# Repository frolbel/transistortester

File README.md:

# TransistorTester with AVR microcontroller

This repository is based on the software repository of the TransistorTester of Markus F. and Karl-Heinz Kubbeler.

The current revision of the authors you can see on the following: [https://www.mikrocontroller.net/svnbrowser/transistortester/](https://www.mikrocontroller.net/svnbrowser/transistortester/?sortby=author)

Initially, this repository is **GitHub** clone of **SVN** repo svn://mikrocontroller.net/transistortester/

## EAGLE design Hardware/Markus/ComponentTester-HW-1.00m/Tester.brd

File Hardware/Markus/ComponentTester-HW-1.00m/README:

------------------------------------------------------------------------------

                  ReadMe for the Component Tester Hardware

         (c) 2013 by Markus Reschke (madires@theca-tabellaria.de)

------------------------------------------------------------------------------

Last edit:  2013-03-22

* About

The Component Tester is based on the project of Markus Frejek [1&2] and the
successor of Karl-Heinz Kübbeler [3&4].

* Safety Advice

The Component Tester is no DMM! It's a simple tester for components capable
of measuring several things. The probes aren't protected in any way and
won't survive higher voltages than 5V. Don't use the tester for live circuits!
Just use it for unsoldered electronic components! If you test a capacitor make
sure it's discharged before connecting the probes. This isn't just the Safety
Sally, your life may be at risk if you connect the probes to a live circuit
or a power supply (or even mains). 

* What's different?

Karl-Heinz has done a realy great documentation of the tester. I recommend
to read it. Therefore I'll tell you just about the differences to the
official release.

* What's in the box?

Following files are in the archive:
- this README
- schematics in PDF format
- schematics and PCB layout for Eagle 6.4.0
- pictures of my Component Tester

* Circuit

The circuit was extended with a current limiting PWM driver for the LED
backlight of the LCD module. The PWM circuit is based on an idea of
Eberhard Haug [5]. You'll find the details of the current sensing resistor
for the current limiter in the schematics. Calculate the proper resistor
values for the LCD module you're using.

The tester has two power supply inputs, one for battery operation (9V) and
another for an external power supply. The LCD backlight is powered by the
latter input only. The supply voltage shouldn't exceed 12VDC because the
low drop voltage regulator supports 13.2V at maximum (add 0.7V for the
reverse protection diode).

* Layout

The layout is optimized for a benchtop-type box and home lab PCB production
without through-hole plating. I recommend to use precision sockets for both
ICs. They allow to solder the pins at the top layer without much trouble.
You might need to grind the top layer pads for the crystal to prevent any
short circuit of the leads via the metal case. Also the drill diameter of
the pads for the ISP pinheader connector could require some rework.

* References

[1] AVR-Transistortester, Markus Frejek,
    Embedded Projects Journal, 2011-11

[2] http://www.mikrocontroller.net/topic/131804
    thread of Markus Frejek, Forum, 2009

[3] http://www.mikrocontroller.net/articles/AVR-Transistortester
    Online documentation of the Transistortester, Online Article, 2009-2011

[4] http://www.mikrocontroller.net/articles/AVR_Transistortester
    Short description of the TransistorTester, Karl-Heinz Kübbeler,
    Online Article, 2012

[5] http://www.led-treiber.de/html/leds_grundlagen.html#PWM-Dimmer
    Description of a LM339 based PWM circuit, Eberhard Haug.

------------------------------------ EOF -------------------------------------

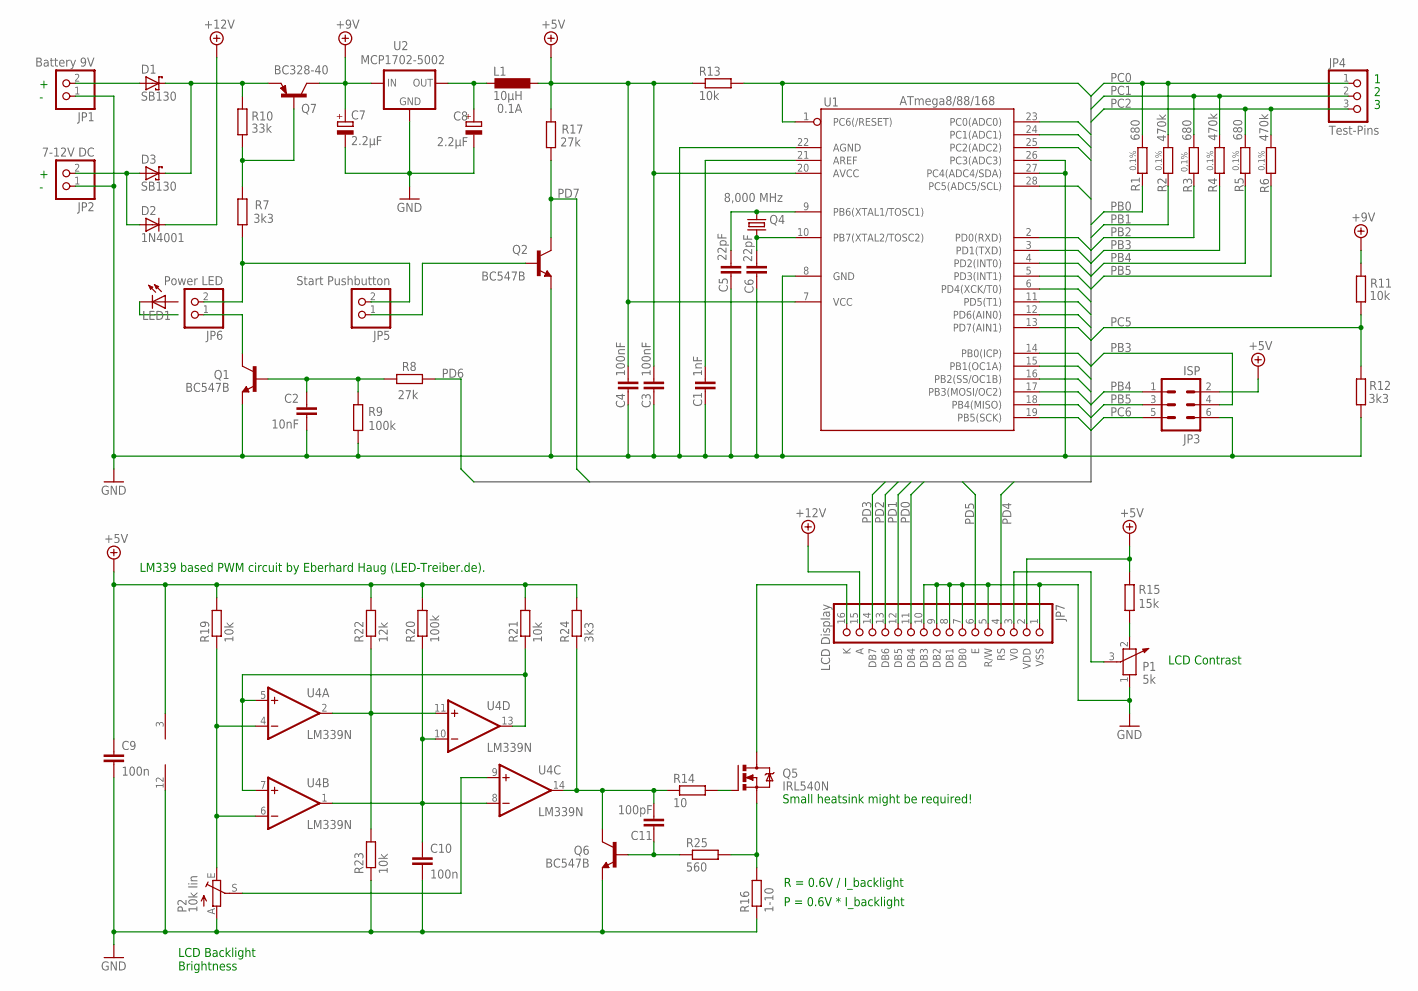
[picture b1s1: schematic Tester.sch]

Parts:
C1: 1nF; C2.5-2
C2: 10nF; C2.5-3
C3, C4: 100nF; C5B3
C5, C6: 22pF; C2.5-3
C7, C8: 2.2µF; E5-5
C9, C10: 100n; C050-024X044
C11: 100pF; C2.5-2
D1, D3: SB130; DIODE-3-5A-V
D2: 1N4001; DIODE-3-5A-V
JP1: Battery 9V; PINHD-1X02
JP2: 7-12V DC; PINHD-1X02
JP3: ISP; ML6
JP4: Test-Pins; PINHD-1X03
JP5: Start Pushbutton; PINHD-1X02
JP6: Power LED; PINHD-1X02
JP7: LCD Display; PINHD-1X16
L1: 10µH; 0204/7
P1: 5k; PT-10
P2: 10k lin; LI10
Q1, Q2, Q6: BC547B; TO92
Q4: 8,000 MHz; HC49/S
Q5: IRL540N; TO220BV
Q7: BC328-40; TO92-EBC
R1, R5: 680; 0207/10; TOLERANCE 0.1%
R2, R4, R6: 470k; 0207/10; TOLERANCE 0.1%
R3: 680; 0207/10; TOLERANCE 0,1%
R7: 3k3; 0207/10
R8, R17: 27k; 0207/2V
R9: 100k; 0207/2V
R10: 33k; 0207/2V
R11, R19, R21: 10k; 0207/2V
R12: 3k3; 0207/2V
R13: 10k; 0207/10
R14: 10; 0207/2V
R15: 15k; 0207/10
R16: 1-10; 0207/10
R20: 100k; 0207/5V
R22: 12k; 0207/5V
R23: 10k; 0207/5V
R24: 3k3; 0207/5V
R25: 560; 0207/5V
U1: ATmega8/88/168; DIL28-3
U2: MCP1702-5002; TO92-LOWDROP
U4: LM339N; DIL14

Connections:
+5V: C3.2, C4.1, C9.1, JP3.2, JP7.2 (VDD), L1.1, R13.1, R15.1, R17.2, R19.2, R20.2, R21.2, R22.2, R24.2, U1.7 (VCC), U1.20 (AVCC), U4.3 (V+)
+9V: C7.+, Q7.C, R11.1, U2.IN
+12V: D2.C, JP7.15 (A)
BL_K: JP7.16 (K), Q5.D
GND: C1.1, C2.2, C3.1, C4.2, C5.1, C6.1, C7.-, C8.-, C9.2, C10.2, JP1.1, JP2.1, JP3.6, JP7.1 (VSS), JP7.5 (R/W), JP7.7 (DB0), JP7.8 (DB1), JP7.9 (DB2), JP7.10 (DB3), P1.1, P2.A, Q1.1 (E), Q2.1 (E), Q6.1 (E), R9.1, R12.1, R16.1, R23.1, U1.8 (GND), U1.22 (AGND), U1.26 (PC3(ADC3)), U1.27 (PC4(ADC4/SDA)), U2.GND, U4.12 (GND)
unnamed: P1.2, R15.2
unnamed: JP7.3 (V0), P1.3
unnamed: Q5.S, R16.2, R25.2
unnamed: R22.1, R23.2, U4.2 (OUT), U4.11 (+IN)
unnamed: D1.C, D3.C, Q7.E, R10.1
unnamed: C10.1, R20.1, U4.1 (OUT), U4.8 (-IN), U4.10 (-IN)
unnamed: R21.1, U4.5 (+IN), U4.7 (+IN), U4.13 (OUT)
unnamed: JP6.1, Q1.3 (C)
unnamed: D1.A, JP1.2
unnamed: C1.2, U1.21 (AREF)
unnamed: C5.2, Q4.2, U1.9 (PB6(XTAL1/TOSC1))
unnamed: C6.2, Q4.1, U1.10 (PB7(XTAL2/TOSC2))
unnamed: JP5.1, Q2.2 (B)
unnamed: P2.E, R19.1, U4.4 (-IN), U4.6 (-IN)
unnamed: P2.S, U4.9 (+IN)
unnamed: C11.2, Q6.3 (C), R14.1, R24.1, U4.14 (OUT)
unnamed: Q5.G, R14.2
unnamed: C11.1, Q6.2 (B), R25.1
unnamed: C8.+, L1.2, U2.OUT
unnamed: JP5.2, JP6.2, R7.1
unnamed: D2.A, D3.A, JP2.2
unnamed: Q7.B, R7.2, R10.2
unnamed: C2.1, Q1.2 (B), R8.2, R9.2
PB0: R1.1, U1.14 (PB0(ICP))
PB1: R2.1, U1.15 (PB1(OC1A))
PB2: R3.1, U1.16 (PB2(SS/OC1B))
PB3: JP3.4, R4.1, U1.17 (PB3(MOSI/OC2))
PB4: JP3.1, R5.1, U1.18 (PB4(MISO))
PB5: JP3.3, R6.1, U1.19 (PB5(SCK))
PC0: JP4.1, R1.2, R2.2, U1.23 (PC0(ADC0))
PC1: JP4.2, R3.2, R4.2, U1.24 (PC1(ADC1))
PC2: JP4.3, R5.2, R6.2, U1.25 (PC2(ADC2))
PC5: R11.2, R12.2, U1.28 (PC5(ADC5/SCL))
PC6: JP3.5, R13.2, U1.1 (PC6(/RESET))
PD0: JP7.11 (DB4), U1.2 (PD0(RXD))
PD1: JP7.12 (DB5), U1.3 (PD1(TXD))
PD2: JP7.13 (DB6), U1.4 (PD2(INT0))
PD3: JP7.14 (DB7), U1.5 (PD3(INT1))
PD4: JP7.4 (RS), U1.6 (PD4(XCK/T0))
PD5: JP7.6 (E), U1.11 (PD5(T1))
PD6: R8.1, U1.12 (PD6(AIN0))
PD7: Q2.3 (C), R17.1, U1.13 (PD7(AIN1))

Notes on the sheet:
R = 0.6V / I_backlight
P = 0.6V * I_backlight
LCD Contrast
LCD Backlight Brightness
Small heatsink might be required!
LM339 based PWM circuit by Eberhard Haug (LED-Treiber.de).

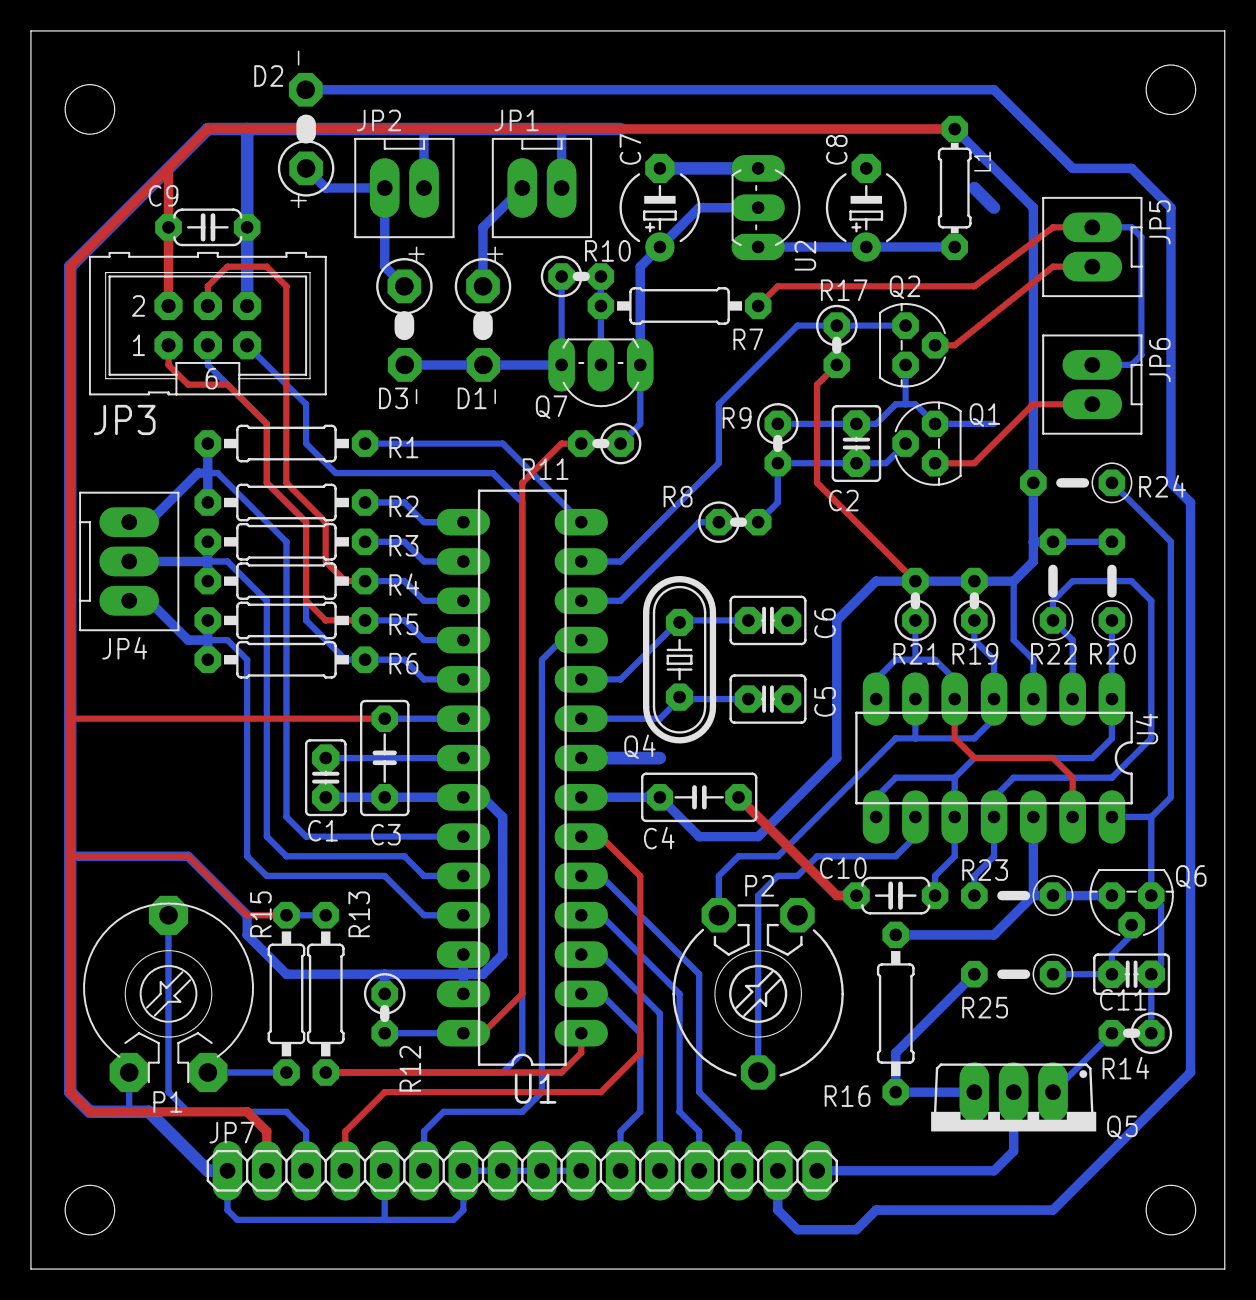
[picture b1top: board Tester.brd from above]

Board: 2 copper layers, 77.1 x 80.0 mm, 57 parts (0 on the bottom side), 47 nets.

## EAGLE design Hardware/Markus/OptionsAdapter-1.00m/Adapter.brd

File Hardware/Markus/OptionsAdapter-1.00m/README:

------------------------------------------------------------------------------

              ReadMe for the Component Tester's Options Adapter

         (c) 2014 by Markus Reschke (madires@theca-tabellaria.de)

------------------------------------------------------------------------------

Last edit:  2014-08-11

* About

The Component Tester is based on the project of Markus Frejek [1&2] and the
successor project of Karl-Heinz Kübbeler [3&4]. The Options Adapter provides
a simple way to extend the basic tester with a rotary encoder for the user
interface and an input stage for the frequency counter function. Both
options are based on the circuits of Karl-Heinz Kübbeler.

* Safety Advice

The Options Adapter doesn't provide any input protection for the frequency
counter besides the AC coupling cap. Don't connect any signal sources with
voltages higher than 5V!

* What's in the box?

Following files are in the archive:
- this README
- schematics in PDF format
- schematics and PCB layout for Eagle 6.5.0 or later
- pictures of my Component Tester with the Options Adapter

* Layout

The layout is optimized for a benchtop-type box and home lab PCB production.
It allows you to mount the adapter perpendicular on the LCD module or in
piggy-back style. You just need to change the pinheaders accordingly.

* References

[1] AVR-Transistortester, Markus Frejek,
    Embedded Projects Journal, 2011-11

[2] http://www.mikrocontroller.net/topic/131804
    thread of Markus Frejek, Forum, 2009

[3] http://www.mikrocontroller.net/articles/AVR-Transistortester
    Online documentation of the Transistortester, Online Article, 2009-2011

[4] http://www.mikrocontroller.net/articles/AVR_Transistortester
    Short description of the TransistorTester, Karl-Heinz Kübbeler,
    Online Article, 2012

------------------------------------ EOF -------------------------------------

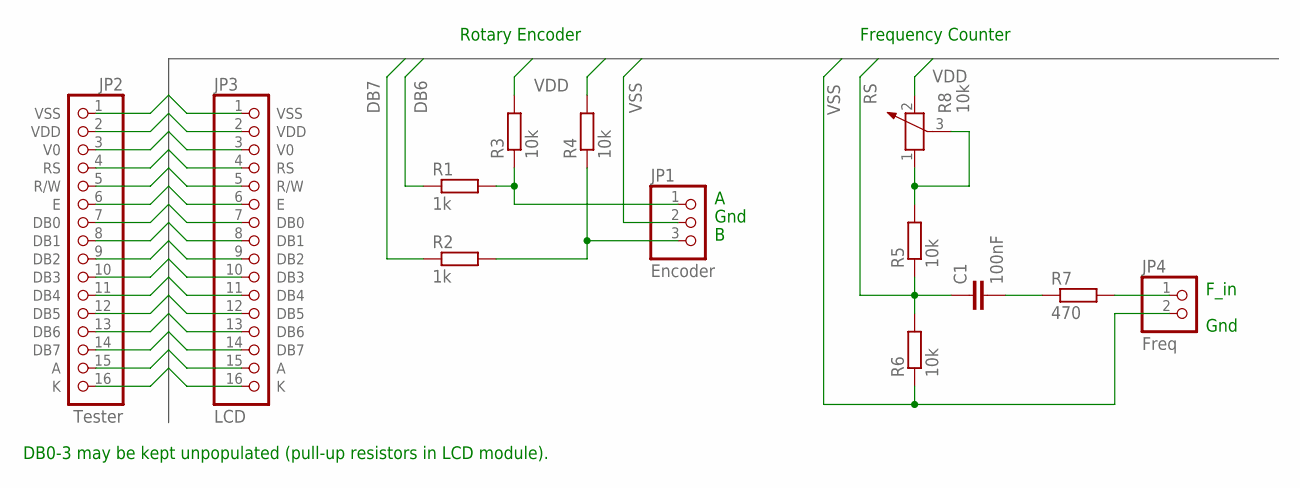
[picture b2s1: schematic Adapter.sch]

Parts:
C1: 100nF; C050-025X075
JP1: Encoder; PINHD-1X03
JP2: Tester; PINHD-1X16
JP3: LCD; PINHD-1X16
JP4: Freq; PINHD-1X02
R1, R2: 1k; 0207/10
R3, R4, R5, R6: 10k; 0207/5V
R7: 470; 0207/5V
R8: 10k; PT-10

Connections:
A: JP2.15 (A), JP3.15 (A)
DB0: JP2.7 (DB0), JP3.7 (DB0)
DB1: JP2.8 (DB1), JP3.8 (DB1)
DB2: JP2.9 (DB2), JP3.9 (DB2)
DB3: JP2.10 (DB3), JP3.10 (DB3)
DB4: JP2.11 (DB4), JP3.11 (DB4)
DB5: JP2.12 (DB5), JP3.12 (DB5)
DB6: JP2.13 (DB6), JP3.13 (DB6), R1.1
DB7: JP2.14 (DB7), JP3.14 (DB7), R2.1
E: JP2.6 (E), JP3.6 (E)
ENC_A: JP1.1, R1.2, R3.1
ENC_B: JP1.3, R2.2, R4.1
K: JP2.16 (K), JP3.16 (K)
unnamed: JP4.1, R7.2
unnamed: R5.2, R8.1, R8.3
unnamed: C1.2, R7.1
RS: C1.1, JP2.4 (RS), JP3.4 (RS), R5.1, R6.2
RW: JP2.5 (R/W), JP3.5 (R/W)
V0: JP2.3 (V0), JP3.3 (V0)
VDD: JP2.2 (VDD), JP3.2 (VDD), R3.2, R4.2, R8.2
VSS: JP1.2, JP2.1 (VSS), JP3.1 (VSS), JP4.2, R6.1

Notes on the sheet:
Gnd
Rotary Encoder
Frequency Counter
F_in
DB0-3 may be kept unpopulated (pull-up resistors in LCD module).

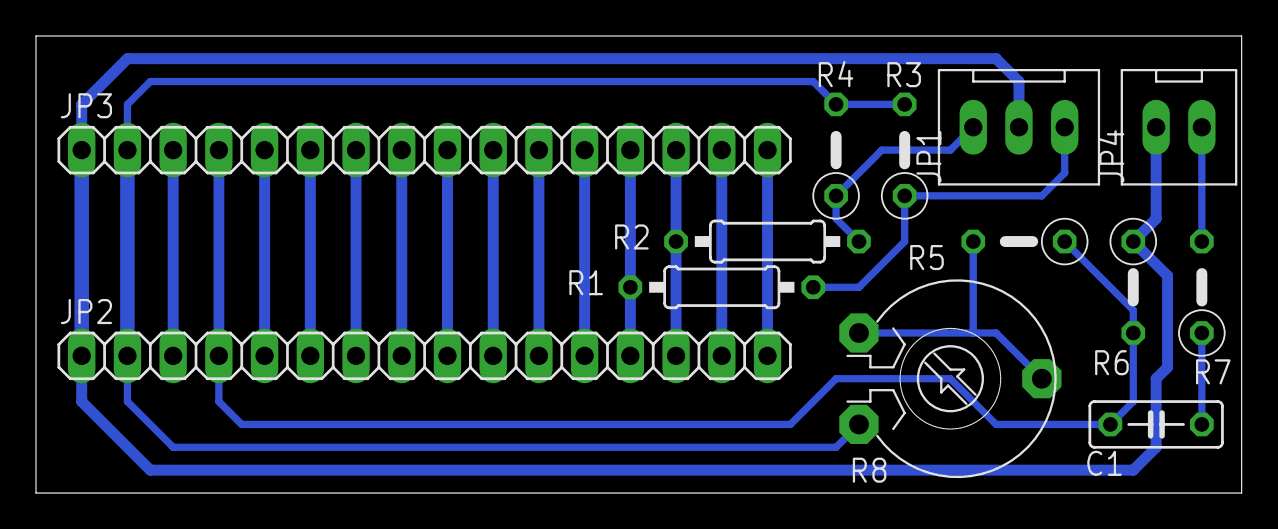
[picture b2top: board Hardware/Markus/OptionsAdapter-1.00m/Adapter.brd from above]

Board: 2 copper layers, 67.0 x 25.4 mm, 13 parts (0 on the bottom side), 21 nets.

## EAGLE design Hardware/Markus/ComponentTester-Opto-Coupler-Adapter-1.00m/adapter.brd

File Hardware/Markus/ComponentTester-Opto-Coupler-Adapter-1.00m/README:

------------------------------------------------------------------------------

                   Component Tester's Opto Coupler Adapter

         rotary encoder and frequency counter, HD44780 compatible

          (c) 2016 by Markus Reschke (madires@theca-tabellaria.de)

------------------------------------------------------------------------------

Last edit:  2016-04-05

* About

The Component Tester is based on the project of Markus Frejek [1&2] and the
successor project of Karl-Heinz Kübbeler [3&4]. The Opto Coupler Adapter
provides a simple way to check opto couplers. It supports BJT types in DIL-4
and DIL-6 packages, and also TRIAC types in DIL-6 package.

* Safety Advice

The Adapter doesn't provide any input protection. Don't connect any external
signal! Only plug in one single opto coupler!

* What's in the box?

Following files are in the archive:
- this README
- schematics in PDF format
- schematics and PCB layout for Eagle 7.5.0 or later

* Layout

The layout is optimized for home lab PCB production.

* References

[1] AVR-Transistortester, Markus Frejek,
    Embedded Projects Journal, 2011-11

[2] http://www.mikrocontroller.net/topic/131804
    thread of Markus Frejek, Forum, 2009

[3] http://www.mikrocontroller.net/articles/AVR-Transistortester
    Online documentation of the Transistortester, Online Article, 2009-2011

[4] http://www.mikrocontroller.net/articles/AVR_Transistortester
    Short description of the TransistorTester, Karl-Heinz Kübbeler,
    Online Article, 2012

------------------------------------ EOF -------------------------------------

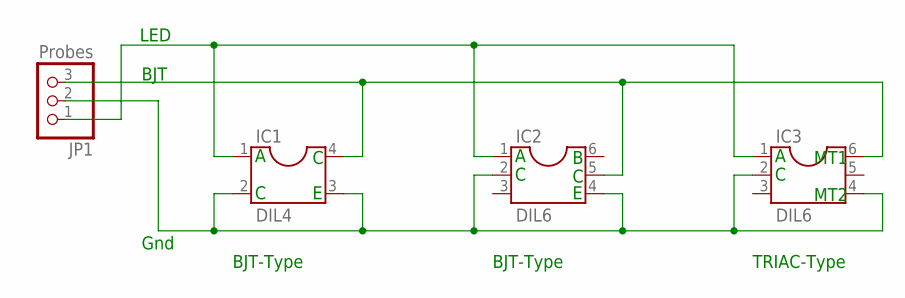
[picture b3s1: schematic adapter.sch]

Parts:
IC1: DIL4; SOCKET-04
IC2, IC3: DIL6; SOCKET-06
JP1: Probes; 1X03/90

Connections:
COLLECTOR: IC1.4, IC2.5, IC3.6, JP1.3
GND: IC1.2, IC1.3, IC2.2, IC2.4, IC3.2, IC3.4, JP1.2
LED: IC1.1, IC2.1, IC3.1, JP1.1

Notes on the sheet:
BJT-Type
TRIAC-Type
Gnd
LED
BJT
MT1
MT2

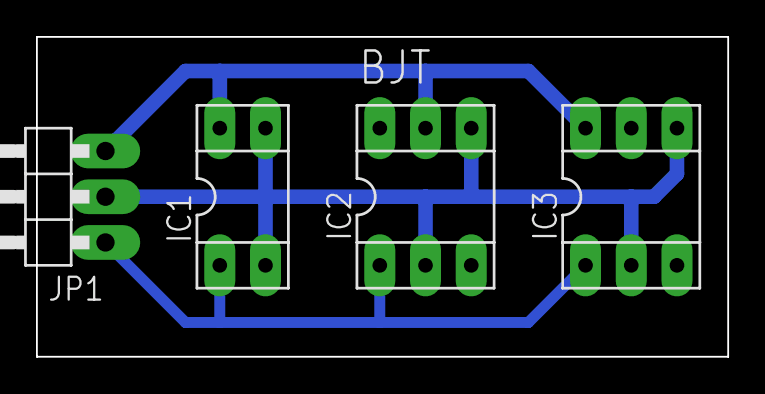
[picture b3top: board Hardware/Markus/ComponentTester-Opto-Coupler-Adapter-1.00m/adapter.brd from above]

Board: 2 copper layers, 38.4 x 17.8 mm, 4 parts (0 on the bottom side), 3 nets.

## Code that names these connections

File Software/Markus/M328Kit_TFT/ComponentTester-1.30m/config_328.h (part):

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#define LCD_PORT         PORTD          /* port data register */
#define LCD_DDR          DDRD           /* port data direction register */
#define LCD_DB_STD                      /* use standard pins 0-3 for DB4-7 */
#define LCD_DB4          PD0            /* port pin used for DB4 */
#define LCD_DB5          PD1            /* port pin used for DB5 */
#define LCD_DB6          PD2            /* port pin used for DB6 */
#define LCD_DB7          PD3            /* port pin used for DB7 */
#define LCD_RS           PD4            /* port pin used for RS */
#define LCD_EN1          PD5            /* port pin used for E */
#define LCD_CHAR_X       16             /* characters per line */
#define LCD_CHAR_Y       2              /* number of lines */
#define FONT_HD44780_INT                /* internal 5x7 font: international */
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#define I2C_PORT         PORTD          /* I2C port data register */
#define I2C_DDR          DDRD           /* I2C port data direction register */
#define I2C_PIN          PIND           /* I2C port input pins register */
#define I2C_SDA          PD0            /* port pin used for SDA */
#define I2C_SCL          PD1            /* port pin used for SCL */
#endif


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/*
 *  ST7565R, SPI interface (bit-bang)
 *  - settings for Electronic Assembly EA DOGM/DOGL128-6
 *  - uses LCD_CS to support rotary encoder in parallel at PD2/3
 */

#if 0
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#define LCD_SPI                         /* SPI interface */
#define LCD_PORT         PORTD          /* port data register */
#define LCD_DDR          DDRD           /* port data direction register */
#define LCD_RESET        PD0            /* port pin used for /RES (optional) */
#define LCD_CS           PD5            /* port pin used for /CS1 (optional) */
#define LCD_A0           PD1            /* port pin used for A0 */
#define LCD_SCL          PD2            /* port pin used for SCL */
#define LCD_SI           PD3            /* port pin used for SI (LCD's data input) */
#define LCD_DOTS_X       128            /* number of horizontal dots */
#define LCD_DOTS_Y       64             /* number of vertical dots */
//#define LCD_FLIP_X                      /* enable horizontal flip */
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#define LCD_SPI                         /* SPI interface */
#define LCD_PORT         PORTD          /* port data register */
#define LCD_DDR          DDRD           /* port data direction register */
#define LCD_RES          PD4            /* port pin used for /RES (optional) */
#define LCD_CS           PD5            /* port pin used for /CS (optional) */
#define LCD_DC           PD3            /* port pin used for D/C */
#define LCD_SCK          PD2            /* port pin used for SCK */
#define LCD_SDI          PD1            /* port pin used for SDI (LCD's data input) */
//#define LCD_SDO          PD0            /* port pin used for SDO (LCD's data output) */
#define LCD_DOTS_X       320            /* number of horizontal dots */
#define LCD_DOTS_Y       240            /* number of vertical dots */
//#define LCD_FLIP_X                      /* enable horizontal flip */
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#define LCD_SPI                         /* SPI interface */
#define LCD_PORT         PORTD          /* port data register */
#define LCD_DDR          DDRD           /* port data direction register */
#define LCD_RES          PD0            /* port pin used for /RESX (optional) */
#define LCD_CS           PD5            /* port pin used for /CSX (optional) */
#define LCD_DC           PD1            /* port pin used for D/CX */
#define LCD_SCL          PD2            /* port pin used for SCL */
#define LCD_SDA          PD3            /* port pin used for SDA */
#define LCD_DOTS_X       128            /* number of horizontal dots */
#define LCD_DOTS_Y       160            /* number of vertical dots */
#define LCD_FLIP_X                      /* enable horizontal flip */
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#define LCD_SPI                         /* SPI interface */
#define LCD_PORT         PORTD          /* port data register */
#define LCD_DDR          DDRD           /* port data direction register */
#define LCD_RES          PD4            /* port pin used for /RES (optional) */
#define LCD_SCE          PD5            /* port pin used for /SCE (optional) */
#define LCD_DC           PD3            /* port pin used for D/C */
#define LCD_SCLK         PD2            /* port pin used for SCLK */
#define LCD_SDIN         PD1            /* port pin used for SDIN (LCD's data input) */
#define LCD_DOTS_X       84             /* number of horizontal dots */
#define LCD_DOTS_Y       48             /* number of vertical dots */
#define LCD_CONTRAST     66             /* default contrast (1-127) */
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#define LCD_SPI                         /* SPI interface */
#define LCD_PORT         PORTD          /* port data register */
#define LCD_DDR          DDRD           /* port data direction register */
#define LCD_RESET        PD4            /* port pin used for /RESET (optional) */
#define LCD_CS           PD5            /* port pin used for CS (optional) */
#define LCD_SCLK         PD2            /* port pin used for SCLK */
#define LCD_SID          PD1            /* port pin used for SID (LCD's data input) */
#define LCD_DOTS_X       128            /* number of horizontal dots */
#define LCD_DOTS_Y       64             /* number of vertical dots */
#define FONT_8X8_H                      /* 8x8 font, horizonally aligned */
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#define LCD_PORT         PORTD          /* port data register */
#define LCD_DDR          DDRD           /* port data direction register */
#define LCD_DB_STD                      /* use standard pins 0-3 for DB4-7 */
#define LCD_DB4          PD0            /* port pin used for DB4 */
#define LCD_DB5          PD1            /* port pin used for DB5 */
#define LCD_DB6          PD2            /* port pin used for DB6 */
#define LCD_DB7          PD3            /* port pin used for DB7 */
#define LCD_RS           PD4            /* port pin used for RS */
#define LCD_EN           PD5            /* port pin used for E */
#define LCD_DOTS_X       128            /* number of horizontal dots */
#define LCD_DOTS_Y       64             /* number of vertical dots */
#define FONT_8X8_H                      /* 8x8 font, horizonally aligned */
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#define ADC_PORT         PORTC     /* ADC port data register */
#define ADC_DDR          DDRC      /* ADC port data direction register */
#define ADC_PIN          PINC      /* port input pins register */
#define TP1              PC0       /* test pin 1 */
#define TP2              PC1       /* test pin 2 */
#define TP3              PC2       /* test pin 3 */

#define TP_ZENER         PC3       /* test pin with 10:1 voltage divider */
#define TP_REF           PC4       /* test pin with 2.5V reference and relay */
#define TP_BAT           PC5       /* test pin with 4:1 voltage divider */


/*
 *  Probe resistors
 *  - For PWM/squarewave output R_RL_2 has to be PB2/OC1B.
 */

#define R_PORT           PORTB     /* port data register */
#define R_DDR            DDRB      /* port data direction register */
#define R_RL_1           PB0       /* Rl (680R) for test pin #1 */
#define R_RH_1           PB1       /* Rh (470k) for test pin #1 */
#define R_RL_2           PB2       /* Rl (680R) for test pin #2 */
#define R_RH_2           PB3       /* Rh (470k) for test pin #2 */
#define R_RL_3           PB4       /* Rl (680R) for test pin #3 */
#define R_RH_3           PB5       /* Rh (470k) for test pin #3 */


/*
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#define CONTROL_PORT     PORTD     /* port data register */
#define CONTROL_DDR      DDRD      /* port data direction register */
#define CONTROL_PIN      PIND      /* port input pins register */
#define POWER_CTRL       PD6       /* controls power (1: on / 0: off) */
#define TEST_BUTTON      PD7       /* test/start push button (low active) */


/*
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#define ENCODER_PORT     PORTD     /* port data register */
#define ENCODER_DDR      DDRD      /* port data direction register */
#define ENCODER_PIN      PIND      /* port input pins register */
#define ENCODER_A        PD1       /* rotary encoder A signal */
#define ENCODER_B        PD3       /* rotary encoder B signal */


/*
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#define KEY_PORT         PORTD     /* port data register */
#define KEY_DDR          DDRD      /* port data direction register */
#define KEY_PIN          PIND      /* port input pins register */
#define KEY_INC          PD1       /* increase push button */
#define KEY_DEC          PD3       /* decrease push button */


/*
 *  frequency counter
 *  - input must be pin PD4/T0
 */

#define COUNTER_PORT     PORTD     /* port data register */
#define COUNTER_DDR      DDRD      /* port data direction register */
#define COUNTER_IN       PD4       /* signal input T0 */


/*
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#define IR_PORT          PORTC     /* port data register */
#define IR_DDR           DDRC      /* port data direction register */
#define IR_PIN           PINC      /* port input pins register */
#define IR_DATA          PC6       /* data signal */


/*
 *  SPI
 *  - hardware SPI uses PB5, PB3 and PB4
 *  - could be already set in display section
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
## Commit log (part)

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2015-09-21 Ccal > 95nF
2015-09-22 Speicheroptimierungen
2015-09-23 alle mega328 mit samplingADC, 10-20nF erforderlich
2015-09-23 Rewrite of the code displaying R and L results: - is now shared between main() and show_Resis_Cap() - also sampling L measurement between TP1:2 and TP2:3 - avoids flashing lcd by overwriting instead 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
2015-09-23 Save 30 bytes of flash by revising sorting of display data for 2 resistors.
2015-09-23 Correction line handling
2015-09-24 Optimierung + Korrektur R-Messung mega168
2015-09-25 Korrektur show_resis
2015-09-25 Korrekturen ...
2015-09-27 Slight simplification of [RL]-mode header line code; also repairs missing [R] if compiled without L-meter support.
2015-09-28 Minor fix for [RL] mode first display line.
2015-09-28 short uncalibrated message with option SHORT_UNCAL_MSG
2015-09-29 some bug-fixes
2015-09-30 Correction no ESR >1000uF
2015-09-30 Corr. SamplingADC with INHIBIT_SLEEP_MODE
2015-10-02 Ueberschreiben der Icons bei 6x8 Font
2015-10-02 5x8 Font von Michael D.
2015-10-03 Vak-Diodes problem with ILI9163,ST7735
2015-10-05 Option WITH_6_SELECTION_MENU from Ahmed M. G.
2015-10-05 PCF8814 Controller with 65 lines
2015-10-05 Correct of range check for graphical display
2015-10-06 remove of test output
2015-10-06 correction of wrong cyrillic fonts length
2015-10-06 more clear display
2015-10-07 Big icons for PCF8812/PCF8814
2015-10-07 automatic selection of menu lines up to 6
2015-10-07 return to old samplingADC.S
2015-10-09 Documentation of SamplingADC option
2015-10-10 Update russian documentation samplingADC
2015-10-11 Update counter version of samplingADC
2015-10-11 1.19m Classic-Version von Markus R.
2015-10-11 kleine Aenderung an samplingADC
2015-10-13 show Icons behind show_data
2015-10-13 Option NO_ICONS_DEMO in Makefile's
2015-10-13 8MHz version shows correct frequency with sampling_lc
2015-10-13 Testversion samplingADC
2015-10-15 new subdirectory mega644_ssd1306I2C
2015-10-18 correction of middle menu entry
2015-10-19 Change of hFE/B switch
2015-10-23 correction of russian documentation
2015-10-23 test version of samplingADC_cnt
2015-10-25 Corrections for russian documentation
2015-10-26 neue samplingADC_cnt
2015-10-28 Update of the sampling_lc code to better use the new samplingADC_cnt mode. Add macros in Transistortester.h for among others calculating pinmask.
2015-11-01 removing debug-output of sampling_lc
2015-11-01 kleine Wartezeit bei Cap for L meas
2015-11-03 Improvements to sampling_lc.c , adaptations for samplingADC_CNT, better sanity checks and prevent wrong dist0 calculation.
2015-11-04 trendy 1.19m von Markus
2015-11-05 Add support for UJT (unijunction transistor) and PUT (programmable UJT).
2015-11-06 Measure capacitance of double diode if compiled with samplingADC, since double diodes are often varicaps.
2015-11-08 Improved detection of PUT.
2015-11-11 New compile option #define big_cap_no_float enables 470 kOhm pull-up during ADC cycle in big cap measurement routine. This prevents detection of spurious big caps when in fact nothing is connected.
2015-11-11 Documented the meaning of the Rddr_[01] and Rport_[01] of samplingADC() with samplingADC_cnt option.
2015-11-11 Minor clarifications in documentation samplingADC() arguments.
2015-11-23 Rewrote samplingADC.S; now takes same arguments as samplingADC_cnt.S (which removed conditional code elsewhere), but has precisely periodic measurements and code is shorter.
2015-11-27 Tausch von Counter1 compare match Interrupts wegen samplingADC
2015-11-30 spezieller PWM-Modus fuer Modellbau Servo mit Option PWM_SERVO
2015-12-01 Correcting error of standard PWM with SVN version 614
2015-12-01 spezieller PWM-Modus fuer Modellbau Servo, Anzeige Pulslaenge
2015-12-04 Fixed silly error in sampling_lc().
2015-12-05 Extra sanity check in peaksearch() to detect spurious peak which comes far too late.
2015-12-05 Removed some useless test data accidentally left in in previous commit.
2015-12-07 Version 1.20m von Markus
2016-01-01 Version 1.21m von Markus R.
2016-01-02 Correction of missing Selection: without POWER_OFF option
2016-01-18 Korrektur Makefile in mega328_wei_st7565
2016-01-23 Patch for TC1604A Display with Option FOUR_LINE_LCD=14
2016-01-24 Ergaenzung der Beschreibung der SamplingADC Funktion
2016-01-24 Neue Option DD_RAM_OFFSET
2016-01-27 russian translation of documentation
2016-01-27 korrektur UJT
2016-02-02 WITH_XTAL adds support for measuring ceramic resonators, and crystals in the range 1 to about 13 MHz, only between TP1 and TP3. Needs 16 MHz clock.
2016-02-03 pinmaskADC mit TXD_MSK
2016-02-03 Show less precision for crystal near 8 MHz because those can't be measured well. Some polishing, saves about 120 bytes of flash.
2016-02-04 Saved 86 bytes of flash at various places in sampling_xtal.c.
2016-02-09 Kein Quarztest fuer grosse Kondensatoren
2016-02-10 Option USE_EEPROM fuer mega328 Makefiles
2016-02-12 Berichtigung fuer NO_NANO Option
2016-02-15 Fehlerkennung XTAL
2016-02-15 Drehencoder Test bei Mega328 nur mit Option WITH_ROTARY_CHECK
2016-02-16 Makefiles with commented option WITH_ROTARY_CHECK
2016-02-17 Improved detection of crystals.
2016-02-17 Correction of crystal data output for 2-line display.
2016-02-19 verhindert Warning
2016-02-19 remove space behind WITH_SamplingADC=1 in Makefile
2016-02-20 Y1 Kanal statt Y2 bei m644 fur HF Quarz mit Option STRIP_GRID_BOARD
2016-02-20 Y1 Kanal statt Y2 bei m644 fur HF Quarz mit Option STRIP_GRID_BOARD=16
2016-02-21 Abschalten des Testers nach Beenden des [C] oder [RL] Auto-Modus
2016-02-24 Fehlende Adresse in main.c ohne Option POWER_OFF
2016-02-24 hFE bzw. B bei BJT mit einer Nachkommastelle
2016-02-24 Improvements to the crystal code: - only try crystals if cap < 100 pF - on weak crystal signals (typ. at high freq.), repeat 4 times and add to improve SNR - better sine approximation in minifourier(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
2016-02-25 Detektion BJT wegen Optokopper mit hFE ab 0.1 angepasst
2016-02-25 Self-initialize two variables to prevent warnings about them not being initialized properly (even though they provably are, conditionally in a loop).
2016-02-26 Aufloesung hFE wegen Optokopper auf 0.01 angepasst
2016-02-26 Korrektur Overflow Problem bei hFE Bestimmung
2016-02-26 Auslagerung CheckUJT Funktion aus main.c
2016-03-02 Saved about 128 bytes of RAM and about 90 bytes of flash in xtal-measurements, by letting samplingADC() write 8-bit rather than 16-bit data. Also fixed incorrect aliasing of ceramic resonators.
2016-03-03 Hilfsfunktion Display_Hz
2016-03-06 f-generator flexibler einstellbar
2016-03-07 Correction of f-generator problem without POWER_OFF
2016-03-28 sure instead of shure correction
2016-03-28 Version 1.22m, Optokoppler, t_on, t_off
2016-03-30 langsamere ISP-Clock fuer make fuses, fuses-crystal, erase
2016-04-05 changed #if in HelpCalibration.c for mega168
2016-04-06 Adapter fuer Optokoppler von Markus
2016-04-21 Support for Arduino UNO
2016-04-22 Support for Arduino UNO, ReadMe
2016-04-22 wiring diagram for Arduino UNO shield
2016-04-22 Arduino UNO shield with LM4040
2016-04-23 Arduino UNO shield with LM4040 Correction
2016-05-08 Assembler-Version von optiboot mit EEprom
2016-05-13 optiboot with automatic size-depending config
2016-05-29 optiboot update and documentation
2016-06-01 correction for mega8, english documentation
2016-06-02 correction for mega328
2016-06-11 corrected russian documentation
2016-06-24 Support for chinese color kit
2016-06-29 Optional menu function for selecting color
2016-07-08 Support for CZECH character set
2016-07-09 correcting wrong sleep_5ms.S
2016-07-12 new 1.23m version from Markus R.
2016-08-01 correction for Arduino Uno shield
2016-08-02 Documentation Chinese Kit
2016-08-04 Russian documentation Chinese Kit
2016-08-05 neue 1.24m trendy von Markus
2016-08-23 In hFE line use beta character rather than B, if available; for now only implemented in 6x8 font.
2016-08-23 Enable interruption by keypress of the ceramic resonator and crystal measurements, since they take a lot of time and can easily be started accidentally.
2016-09-09 support for lower software baud rate
2016-09-25 Neue trendy Version von Markus mit ATmega644/1284 Support
2016-10-16 ESR asbove 20nF, Support for ILI9341
2016-10-17 Symbol Beta with graphic displays
2016-10-25 NPNp oder PNPn nicht automatisch mit hFE unter 5
2016-11-07 serial output with more CR/LF, ILI9341 with 8x12 font
2016-11-07 partitial documentation of a new wei_st7565
2016-11-23 remove of double Vloss output for 2-line display
2016-12-02 Version 1.26m von Markus
2016-12-17 Beschreibung ESR Messung mit 2us Pulsen
2016-12-17 function switch_tester_off
2016-12-20 russian translation ESR measurement with 2us pulses
2016-12-25 correction of capacity limit for ESR mwasurement
2017-01-15 ESR measurement with 470k
2017-01-15 correction of features
2017-01-19 additional 470k resistor for the half amount of single ESR measurements
2017-01-19 Abschluss der 1.12k Version
2017-01-19 Nachtrag russische Doku 1.12k Version
2017-01-22 Korrektur finale 1.12k Version
2017-02-02 additional newline characters for serial output
2017-02-18 1.12k documentation update for frequency selection
2017-02-18 russian 1.12k documentation update for frequency selection
2017-02-18 english,russian 1.12k documentation update for frequency selection
2017-02-19 Ende der Frequenzerzeugung mit 2s Tastendruck
2017-02-20 adding the _NUMERATOR and _DENOMINATOR options to the documentation
2017-02-21 adding the _NUMERATOR and _DENOMINATOR options to the russian docu
2017-02-23 Version 1.27m von Markus
2017-03-14 wave detection in sampling_lc modified
2017-03-15 range of get_log extended
2017-03-18 Russian translation of documentation ver. 722
2017-03-28 Hardware Entwurf von Max
2017-04-11 Version 1.28m von Markus R.
2017-05-06 Fortschrittsanzeige
2017-05-07 Anzeige der Cut-off Spannung bei JFET/D-MOS
2017-05-18 Korrektur Tschechisch
2017-05-23 Modified samplingADC.S to guarantee correct placement in memory, regardless of size of other pieces of code.
2017-05-23 Made text "DC Pwr Mode" configurable from Makefile. (Useful e.g. for devices which use USB rather than an AC/DC power adapter.)
2017-05-23 Enable 470k resistor from HiPin to ground during pin discharge, to prevent not detecting completion of discharge if there's some leakage in the circuit (e.g., via protection diodes).
2017-05-24 For JFETs only show cut-off voltage if measured value is not near 5 V (as then JFET may not really have been cut-off).
    Added measurement of I_{DSS} for JFET.
    Compliation onditional on #ifdef FET_Idss.
    So far only for N-channel, and output only on text display.
2017-05-26 zusaetzliche Tabellen der Anschlußbelegung
2017-05-26 Anzeige Idss mit Option FET_Idss
2017-05-27 neue russische Doku-Uebersetzung + Korrektur der englischen Doku
2017-05-27 Trivial corrections to source code comments.
2017-07-07 Version 1.29m von Markus
2017-07-26 corrections for Dutch language by D. Mantione
2017-08-13 support for ext voltage greater 63V possible
2017-08-30 support for francais language from C Bricaud
2017-09-29 Controller name corrected to NT7108
2017-10-05 Berechnung Idss bei JFETs
2017-10-08 Abschaltbare Frequenz-Zaehler Funktion
2017-10-09 Update russian documentation
2017-10-21 Version 1.30m von Markus R.
2017-10-31 selectable prescaler for frequency measurement and some optimizing
2017-12-28 A branch of the repository has been created which is based on version 1.30m of Transistor Tester Markus F.
2017-12-28 Add TT-Markus_Reschke Ru 18.10.17.pdf
2017-12-28 Modified for M328Kit_TFT_1.30mRus(16MHz)
2017-12-28 Add ".gitignore"
2017-12-28 Modified ".gitignore"
2017-12-28 A branch of the repository has been created which is based on current version of Transistor Tester Karl-Heinz K.
2017-12-28 Update after added branch
2017-12-28 Modified for M328Kit_TFT_Rus(16MHz)

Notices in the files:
Software/Markus/M328Kit_TFT/ComponentTester-1.30m/config_328.h:
(c) 2012-2017 by Markus Reschke
Hardware/Markus/ComponentTester-Opto-Coupler-Adapter-1.00m/adapter.sch:
COPYRIGHT: (c) 2016 by Markus Reschke
